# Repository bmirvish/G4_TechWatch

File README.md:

# G4_TechWatch
Smartwatch Milestone 2022

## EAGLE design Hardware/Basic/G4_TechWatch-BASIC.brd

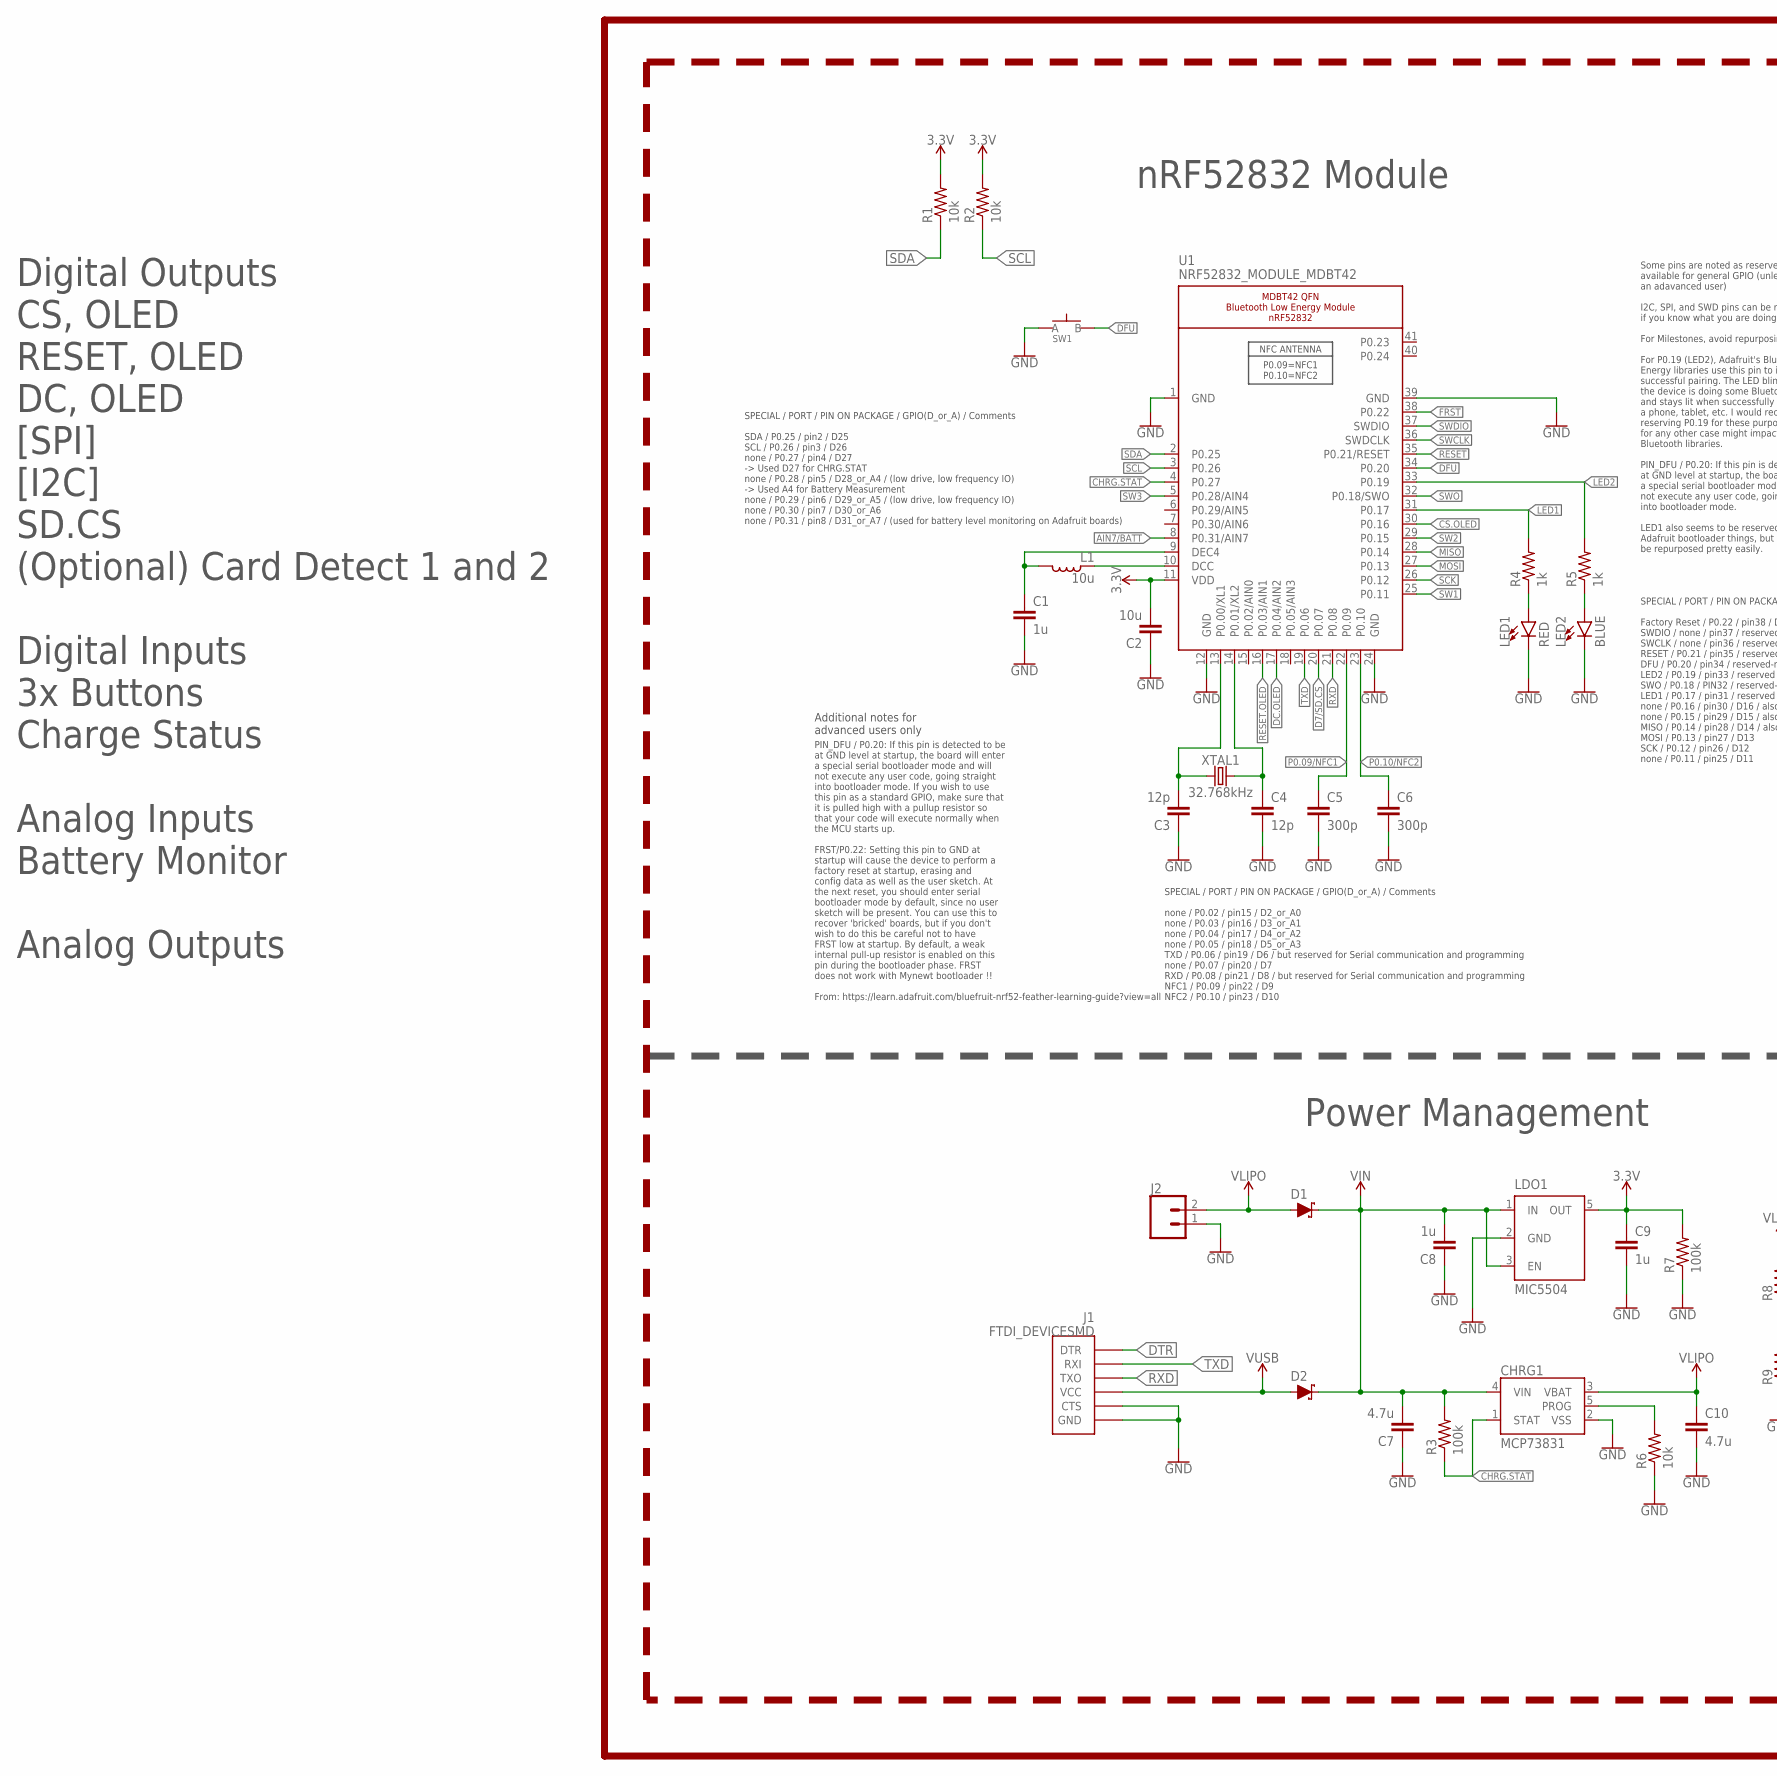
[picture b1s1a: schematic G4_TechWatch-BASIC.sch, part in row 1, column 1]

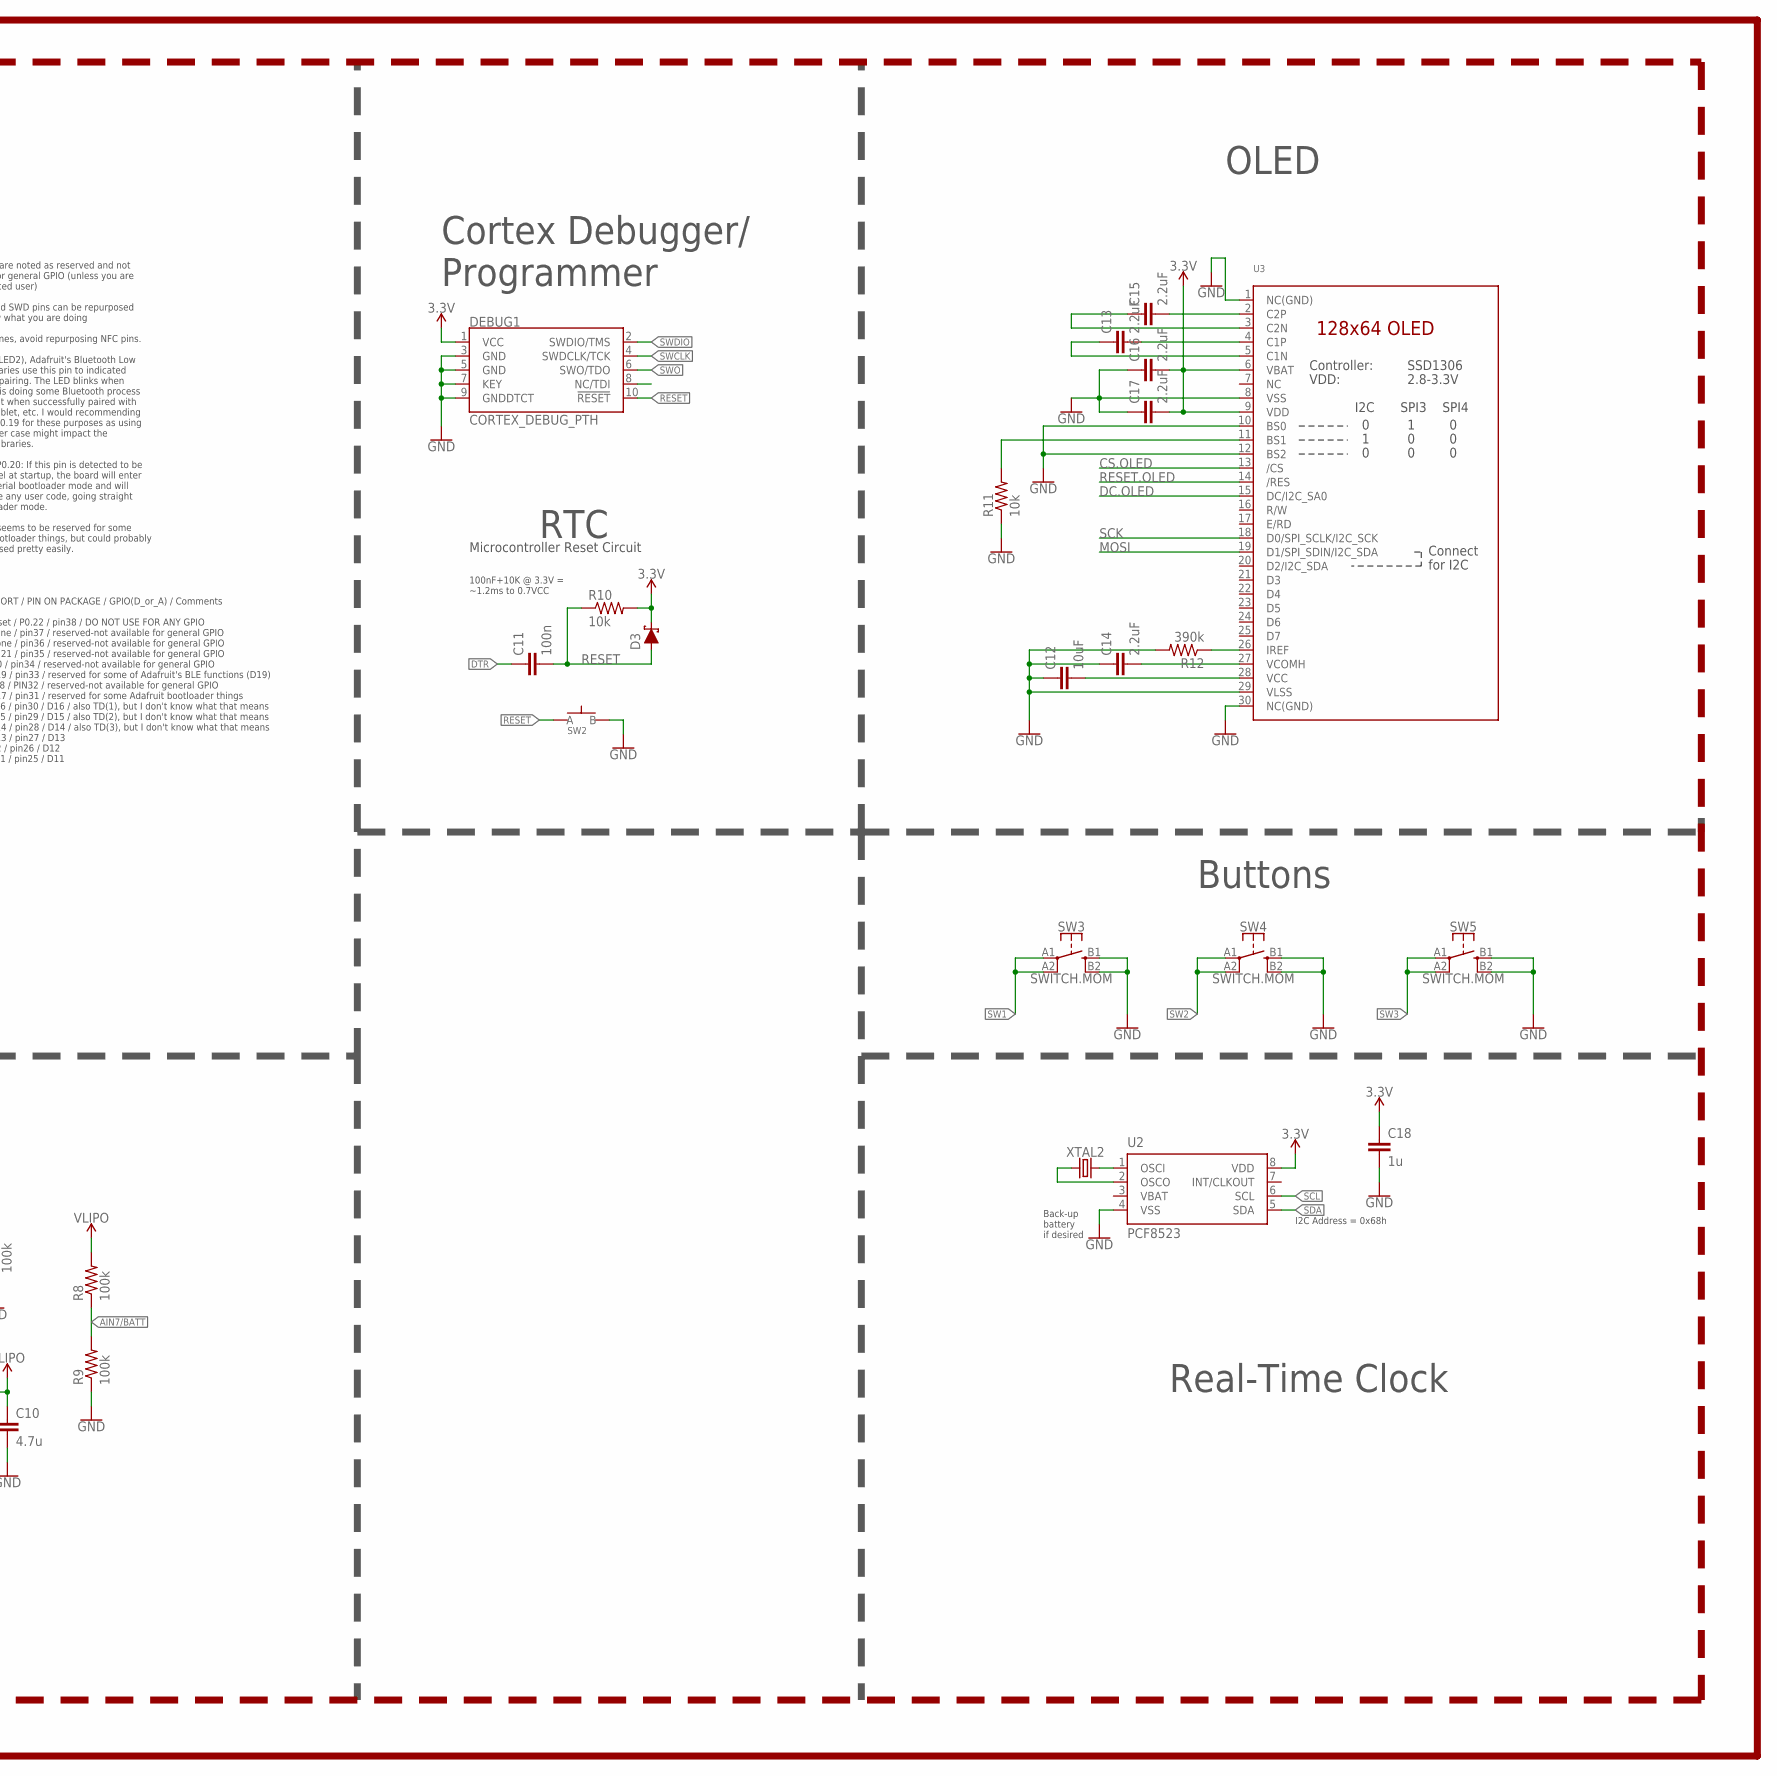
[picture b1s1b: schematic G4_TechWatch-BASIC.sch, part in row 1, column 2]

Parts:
C1, C8, C9, C18: 1u; C0603
C2: 10u; C0805
C3, C4: 12p; C0603
C5, C6: 300p; C0603
C7, C10: 4.7u; C0603
C11: 100n; C0603
C12: 10uF; C0603
C13, C14, C15, C16, C17: 2.2uF; C0402
CHRG1: MCP73831; SOT23-5
D1, D2, D3: SCHOTTKY-USC; USC
DEBUG1: CORTEX_DEBUG_PTH; 2X5-PTH-1.27MM
J1: FTDI_DEVICESMD; FTDI-SMD
J2: CONN_02; 1X02
L1: 10u; L0603
LDO1: MIC5504; SOT23-5
LED1: RED; LED-0603
LED2: BLUE; LED-0603
R1, R2, R6, R10, R11: 10k; R0603
R3, R7, R8, R9: 100k; R0603
R4, R5: 1k; R0603
R12: 390k; R0603
SW1, SW2: SPST-PTS830GG140-COPY.1-3; BUTTON-GULLWING
SW3, SW4, SW5: SWITCH.MOM; TACTILE_SWITCH_SMD_6.2MM_TALL
U1: NRF52832_MODULE_MDBT42; BLE_MODULE_RAYTAC_MDBT42
U2: PCF8523; SO8; DIGIKEY 568-5306-1-ND
U3: DISP_OLED_UG-2864HSWEG01-NO-WRAPAROUND; UG-2864HSWEG01_0.96IN_NO-WRAPAROUND
XTAL1: 32.768kHz; 2-SMD.NOLEAD.2.0MMTO1.2MM
XTAL2: 32.7680kHz; 2-SMD.NOLEAD.2.0MMTO1.2MM

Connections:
3.3V: C2.2, C9.1, C16.2, C17.2, C18.1, D3.- (C), DEBUG1.1 (VCC), LDO1.5 (OUT), R1.2, R2.2, R7.2, R10.2, U1.11 (VDD), U2.8 (VDD), U3.6 (VBAT), U3.9 (VDD)
AIN7/BATT: R8.1, R9.2, U1.8 (P0.31/AIN7)
CHRG.STAT: CHRG1.1 (STAT), R3.1, U1.4 (P0.27)
CS.OLED: U1.30 (P0.16), U3.13 (/CS)
D7/SD.CS: U1.20 (P0.07)
DC.OLED: U1.17 (P0.04/AIN2), U3.15 (DC/I2C_SA0)
DFU: SW1.3 (B), U1.34 (P0.20)
DTR: C11.1, J1.DTR
FRST: U1.38 (P0.22)
GND: C1.2, C2.1, C3.1, C4.2, C5.2, C6.2, C7.1, C8.1, C9.2, C10.2, C12.1, C14.1, C16.1, C17.1, C18.2, CHRG1.2 (VSS), DEBUG1.3 (GND), DEBUG1.5 (GND), DEBUG1.7 (KEY), DEBUG1.9 (GNDDTCT), J1.CTS, J1.GND, J2.1, LDO1.2 (GND), LED1.C, LED2.C, R6.1, R7.1, R9.1, R11.1, R12.2, SW1.1 (A), SW2.3 (B), SW3.B1 (3), SW3.B2 (4), SW4.B1 (3), SW4.B2 (4), SW5.B1 (3), SW5.B2 (4), U1.1 (GND), U1.12 (GND), U1.24 (GND), U1.39 (GND), U2.4 (VSS), U3.1 (NC(GND)), U3.8 (VSS), U3.10 (BS0), U3.12 (BS2), U3.29 (VLSS), U3.30 (NC(GND))
LED1: R4.2, U1.31 (P0.17)
LED2: R5.2, U1.33 (P0.19)
MISO: U1.28 (P0.14)
MOSI: U1.27 (P0.13), U3.19 (D1/SPI_SDIN/I2C_SDA)
unnamed: R11.2, U3.11 (BS1)
unnamed: R12.1, U3.26 (IREF)
unnamed: C15.2, U3.2 (C2P)
unnamed: C3.2, U1.13 (P0.00/XL1), XTAL1.P$1 (1)
unnamed: C15.1, U3.3 (C2N)
unnamed: C4.1, U1.14 (P0.01/XL2), XTAL1.P$2 (2)
unnamed: C13.2, U3.4 (C1P)
unnamed: C13.1, U3.5 (C1N)
unnamed: LED1.A, R4.1
unnamed: LED2.A, R5.1
unnamed: L1.1, U1.10 (DCC)
unnamed: C1.1, L1.2, U1.9 (DEC4)
unnamed: C12.2, U3.28 (VCC)
unnamed: C14.2, U3.27 (VCOMH)
unnamed: CHRG1.5 (PROG), R6.2
unnamed: U2.2 (OSCO), XTAL2.P$1 (1)
unnamed: U2.1 (OSCI), XTAL2.P$2 (2)
P0.09/NFC1: C5.1, U1.22 (P0.09)
P0.10/NFC2: C6.1, U1.23 (P0.10)
RESET: C11.2, D3.+ (A), DEBUG1.10 (!RESET), R10.1, SW2.1 (A), U1.35 (P0.21/RESET)
RESET.OLED: U1.16 (P0.03/AIN1), U3.14 (/RES)
RXD: J1.TXO, U1.21 (P0.08)
SCK: U1.26 (P0.12), U3.18 (D0/SPI_SCLK/I2C_SCK)
SCL: R2.1, U1.3 (P0.26), U2.6 (SCL)
SDA: R1.1, U1.2 (P0.25), U2.5 (SDA)
SW1: SW3.A1 (1), SW3.A2 (2), U1.25 (P0.11)
SW2: SW4.A1 (1), SW4.A2 (2), U1.29 (P0.15)
SW3: SW5.A1 (1), SW5.A2 (2), U1.5 (P0.28/AIN4)
SWCLK: DEBUG1.4 (SWDCLK/TCK), U1.36 (SWDCLK)
SWDIO: DEBUG1.2 (SWDIO/TMS), U1.37 (SWDIO)
SWO: DEBUG1.6 (SWO/TDO), U1.32 (P0.18/SWO)
TXD: J1.RXI, U1.19 (P0.06)
VBAT: U2.3 (VBAT)
VIN: C7.2, C8.2, CHRG1.4 (VIN), D1.- (C), D2.- (C), LDO1.1 (IN), LDO1.3 (EN), R3.2
VLIPO: C10.1, CHRG1.3 (VBAT), D1.+ (A), J2.2, R8.2
V_USB: D2.+ (A), J1.VCC

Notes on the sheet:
Microcontroller Reset Circuit
100nF+10K @ 3.3V = ~1.2ms to 0.7VCC
SPECIAL / PORT / PIN ON PACKAGE / GPIO(D_or_A) / Comments SDA / P0.25 / pin2 / D25 SCL / P0.26 / pin3 / D26 none / P0.27 / pin4 / D27 -> Used D27 for CHRG.STAT none / P0.28 / pin5 / D28_or_A4 / (low drive, low frequency IO) -> Used A4 for Battery Measurement none / P0.29 / pin6 / D29_or_A5 / (low d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
SPECIAL / PORT / PIN ON PACKAGE / GPIO(D_or_A) / Comments none / P0.02 / pin15 / D2_or_A0 none / P0.03 / pin16 / D3_or_A1 none / P0.04 / pin17 / D4_or_A2 none / P0.05 / pin18 / D5_or_A3 TXD / P0.06 / pin19 / D6 / but reserved for Serial communication and programming none / P0.07 / pin20 / D7 RXD / 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
SPECIAL / PORT / PIN ON PACKAGE / GPIO(D_or_A) / Comments Factory Reset / P0.22 / pin38 / DO NOT USE FOR ANY GPIO SWDIO / none / pin37 / reserved-not available for general GPIO SWCLK / none / pin36 / reserved-not available for general GPIO RESET / P0.21 / pin35 / reserved-not available for general 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
Some pins are noted as reserved and not available for general GPIO (unless you are an adavanced user) I2C, SPI, and SWD pins can be repurposed if you know what you are doing For Milestones, avoid repurposing NFC pins. For P0.19 (LED2), Adafruit's Bluetooth Low Energy libraries use this pin to indic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
PIN_DFU / P0.20: If this pin is detected to be at GND level at startup, the board will enter a special serial bootloader mode and will not execute any user code, going straight into bootloader mode. If you wish to use this pin as a standard GPIO, make sure that it is pulled high with a pullup resis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
Additional notes for advanced users only
I2C Address = 0x68h
Back-up battery if desired
nRF52832 Module
OLED
Power Management
Buttons
Real-Time Clock
Cortex Debugger/ Programmer
RTC
Digital Outputs CS, OLED RESET, OLED DC, OLED [SPI] [I2C] SD.CS (Optional) Card Detect 1 and 2 Digital Inputs 3x Buttons Charge Status Analog Inputs Battery Monitor Analog Outputs

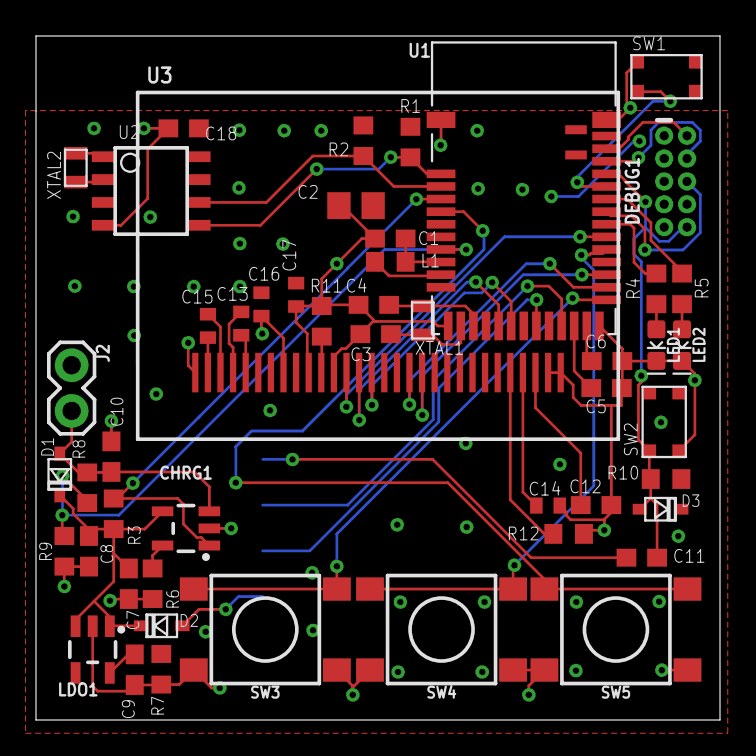
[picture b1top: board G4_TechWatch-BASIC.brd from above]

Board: 2 copper layers, 38.0 x 38.0 mm, 51 parts (1 on the bottom side), 46 nets.

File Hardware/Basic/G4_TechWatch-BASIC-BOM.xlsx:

Design Name -- Revision Code / Designer or Organization Name |  |  |  |  |  |  |  |  |  |  | Total | 10.700000000000001 | Total (in Bulk) | 9.9516000000000009
BOM # | Comment | Designator | Description | Mounting Type | Package | Manufacturer | Manufacturer Part Number | Supplier | Supplier Part Number | Price per unit | Quantity | Total | Per 100 | Total
1 | NRF52832 | U1 | BLE Capable Microcontroller | SMD | 41-SMD Module | Raytac | MDBT42Q-512KV2 | Digi-Key | 3271-MDBT42Q-512KV2-ND | 9.9 | 1 | 9.9 | 9.9 | 9.9
2 | BUTTON-GULLWING | SW1,SW2 |  | SMD |  |  |  | Digi-Key |  |  |  | 0 |  | 0
3 | TACTILE_SWITCH_SMD_6.2MM_TALL | SW3,SW4,SW5 |  | SMD |  |  |  | Digi-Key |  |  |  | 0 |  | 0
4 | 10uH Inductor | L1 |  | SMD | 0603 |  |  | Digi-Key |  |  |  | 0 |  | 0
5 | 10k resistor | R1,R2,R10,R11 | 10 kOhms ±1% 0.1W, 1/10W Chip Resistor 0603 (1608 Metric) Automotive AEC-Q200 T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 | SMD | 0603 | Stackpole Electronics Inc | RMCF0603FT10K0 | Digi-Key | RMCF0603FT10K0CT-ND | 0.1 | 4 | 0.4 | 6.7999999999999996E-3 | 2.7199999999999998E-2
6 | 1uF capacitor | C1 | 1µF ±10% 25V Ceramic Capacitor X5R 0603 (1608 Metric) | SMD | 0603 | Samsung Electro-Mechanics | CL10A105KA8NNNC | Digi-Key | 1276-1102-1-ND | 0.1 |  | 0 | 1.8499999999999999E-2 | 0
7 | 100k resistor | R3,R7,R8,R9 | 100 kOhms ±1% 0.1W, 1/10W Chip Resistor 0603 (1608 Metric) Automotive AEC-Q200 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 | SMD | 0603 | Stackpole Electronics Inc | RMCF0603FT100K | Digi-Key | RMCF0603FT100KCT-ND | 0.1 | 4 | 0.4 | 6.1000000000000004E-3 | 2.4400000000000002E-2
8 | 1k resistor | R4,R5 |  | SMD | 0603 | Stackpole Electronics Inc |  | Digi-Key |  |  |  | 0 |  | 0
9 | 390k resistor | R12 |  | SMD | 0603 | Stackpole Electronics Inc |  | Digi-Key |  |  |  | 0 |  | 0
10 | 1uF capacitor | C1,C8,C9,C18 |  | SMD | 0603 | Samsung Electro-Mechanics |  | Digi-Key |  |  |  | 0 |  | 0
11 | 10uF capacitor | C2,C12 |  | SMD | 0805 | Samsung Electro-Mechanics |  | Digi-Key |  |  |  | 0 |  | 0
12 | 300pF capacitor | C5,C6 |  | SMD | 0603 | Samsung Electro-Mechanics |  | Digi-Key |  |  |  | 0 |  | 0
13 | 4.7uF capacitor | C7,C10 |  | SMD | 0603 | Samsung Electro-Mechanics |  | Digi-Key |  |  |  | 0 |  | 0
14 | 100nF capacitor | C11 |  | SMD | 0603 | Samsung Electro-Mechanics |  | Digi-Key |  |  |  | 0 |  | 0
15 | 32.768kHz Oscillator | XTAL1 | 2-SMD.NOLEAD.2.0MMTO1.2MM (Version 1 + Edits) | SMD |  |  |  | Digi-Key |  |  |  | 0 |  | 0
16 | RED SMD LED | LED1 |  | SMD | 0603 |  |  | Digi-Key |  |  |  | 0 |  | 0
17 | BLUE SMD LED | LED2 |  | SMD | 0603 |  |  | Digi-Key |  |  |  | 0 |  | 0
18 |  |  |  |  |  |  |  | Digi-Key |  |  |  | 0 |  | 0
19 |  |  |  |  |  |  |  | Digi-Key |  |  |  | 0 |  | 0
20 |  |  |  |  |  |  |  | Digi-Key |  |  |  | 0 |  | 0

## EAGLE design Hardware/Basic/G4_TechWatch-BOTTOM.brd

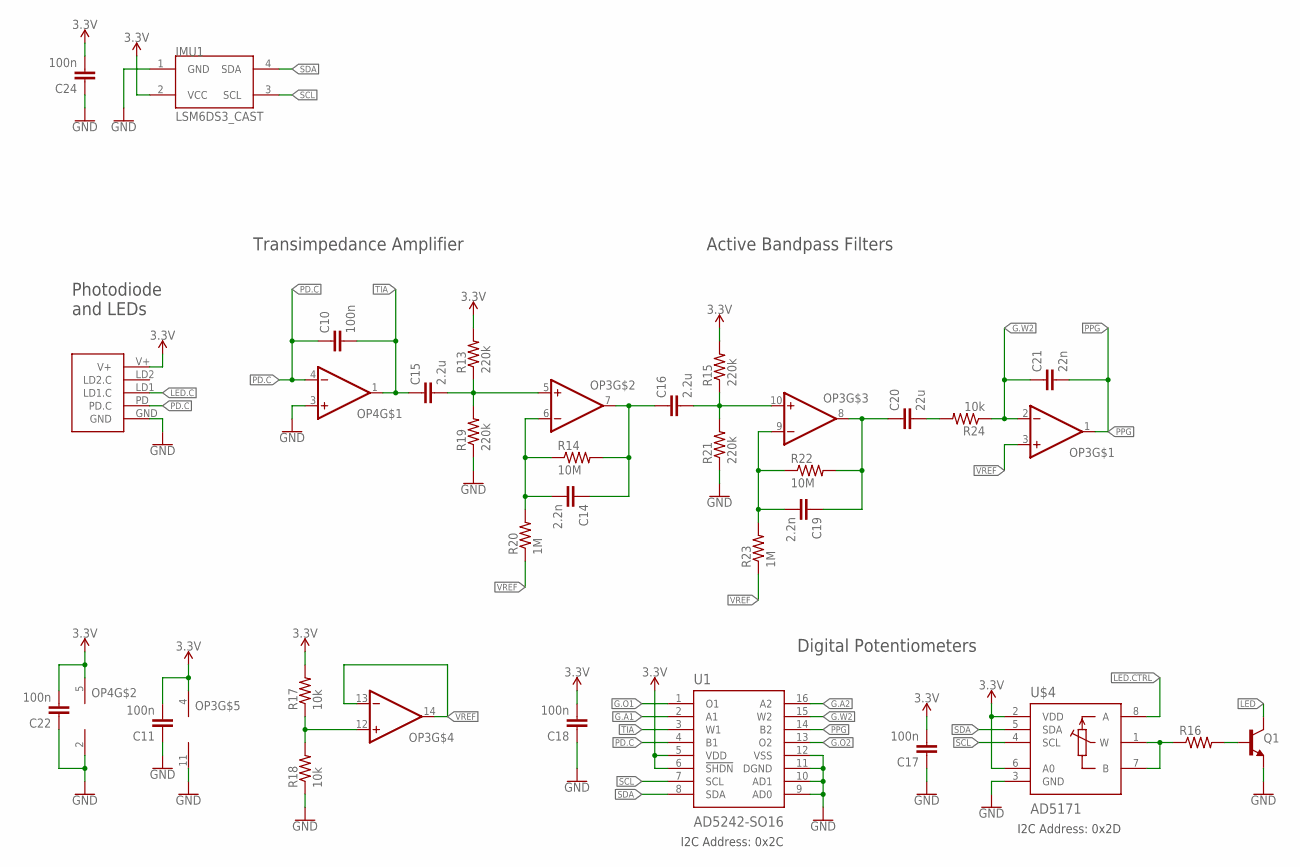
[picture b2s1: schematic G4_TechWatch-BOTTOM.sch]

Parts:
C10, C11, C17, C18, C22, C24: 100n; C0603
C14, C19: 2.2n; C0603
C15, C16: 2.2u; C0603
C20: 22u; C0603
C21: 22n; C0603
IMU1: LSM6DS3_CAST
OP3: OP-QUAD-SO14; SO14
OP4: OP-SINGLEOT; SOT23-5
Q1: NPN-GENERIC; SOT23-3
R13, R15, R19, R21: 220k; R0603
R14, R22: 10M; R0603
R16: RESISTOR0603; R0603
R17, R18: 10k; R0402
R20, R23: 1M; R0603
R24: 10k; R0603
U1: AD5242-SO16; SO16
U$3: PPG.MODULE.2
U$4: AD5171; SOT-23-8

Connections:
3.3V: C11.2, C17.2, C18.2, C22.2, C24.2, IMU1.2 (VCC), OP3.4 (V+), OP4.5 (V+), R13.2, R15.2, R17.2, U1.5 (VDD), U1.6 (!SHDN), U$3.V+, U$4.2 (VDD), U$4.6 (A0)
G.A1: U1.2 (A1)
G.A2: U1.16 (A2)
G.O1: U1.1 (O1)
G.O2: U1.13 (O2)
G.W2: C21.1, OP3.2 (-IN), R24.1, U1.15 (W2)
GND: C11.1, C17.1, C18.1, C22.1, C24.1, IMU1.1 (GND), OP3.11 (V-), OP4.2 (V-), OP4.3 (+IN), Q1.2 (E), R18.1, R19.1, R21.1, U1.9 (AD0), U1.10 (AD1), U1.11 (DGND), U1.12 (VSS), U$3.GND, U$4.3 (GND)
LED: Q1.3 (C)
LED.C: U$3.LD1 (LD1.C)
LED.CTRL: U$4.8 (A)
unnamed: Q1.1 (B), R16.2
unnamed: R16.1, U$4.1 (W), U$4.7 (B)
unnamed: OP3.12 (+IN), R17.1, R18.2
unnamed: C15.2, OP3.5 (+IN), R13.1, R19.2
unnamed: C14.2, OP3.6 (-IN), R14.1, R20.2
unnamed: C14.1, C16.1, OP3.7 (OUT), R14.2
unnamed: C16.2, OP3.10 (+IN), R15.1, R21.2
unnamed: C19.2, OP3.9 (-IN), R22.1, R23.2
unnamed: C19.1, C20.1, OP3.8 (OUT), R22.2
unnamed: C20.2, R24.2
PD.C: C10.1, OP4.4 (-IN), U1.4 (B1), U$3.PD (PD.C)
PPG: C21.2, OP3.1 (OUT), U1.14 (B2)
SCL: IMU1.3 (SCL), U1.7 (SCL), U$4.4 (SCL)
SDA: IMU1.4 (SDA), U1.8 (SDA), U$4.5 (SDA)
TIA: C10.2, C15.1, OP4.1 (OUT), U1.3 (W1)
VREF: OP3.3 (+IN), OP3.13 (-IN), OP3.14 (OUT), R20.1, R23.1

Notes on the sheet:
Photodiode and LEDs
Active Bandpass Filters
Digital Potentiometers
Transimpedance Amplifier
I2C Address: 0x2C
I2C Address: 0x2D

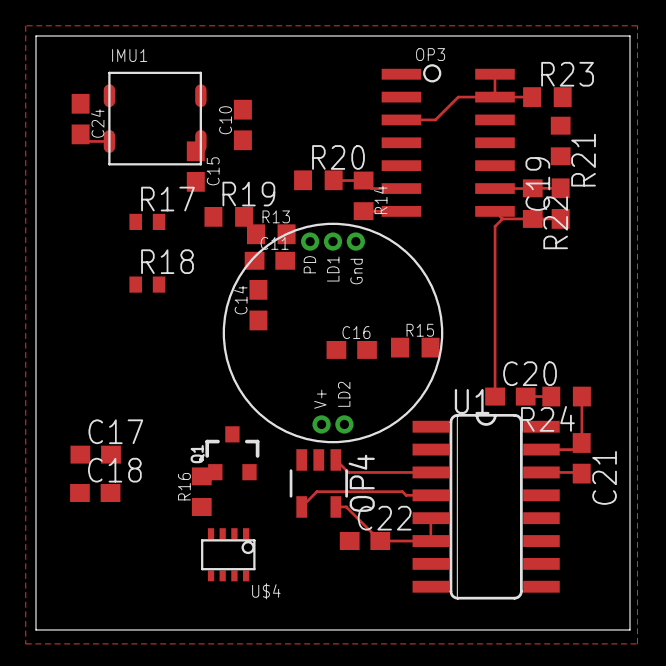
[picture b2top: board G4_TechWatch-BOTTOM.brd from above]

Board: 2 copper layers, 33.0 x 33.0 mm, 31 parts (0 on the bottom side), 19 nets.

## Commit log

2022-09-08 Features List Added
2022-09-08 Updated Watch Features Doc
2022-09-12 Initial Setup Commit
2022-09-14 First Save Point for Board
2022-09-15 End Of Class Schematic
2022-09-21 Updated Schematics
2022-09-21 Removed Bottom Board
2022-09-21 Schematic Step 1 Done
2022-09-22 End of Class 09/21/2022
2022-09-28 Weekly commit for class
2022-09-28 Commit before leaving class
2022-10-04 Board Completed
2022-10-05 Added Ground Vias
2022-10-19 Added Missing values, fixed silkscreen and OLED spacing
2022-10-26 BOM Ver 1 Finished
2022-10-26 Added missing parts
